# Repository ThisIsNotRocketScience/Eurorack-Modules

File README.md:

View this project on [CADLAB.io](https://cadlab.io/node/837). 

# Eurorack-Modules

This is the central repo for all the "This is not Rocket Science" eurorack modular synth modules.

Please refer to the "Production" folder if you are looking for boards to build. You will find all the design & firmware files for our latest production versions. Artwork is NOT included. Be creative. 

All our current development & experiments can be found in the "Development" folder

Sourcecode to the firmware can be found in the Eurorack-KDS repository

Tools needed:

- Eagle 7+
- Kinetis Development Studio (or whatever the latest NXP/freescale IDE is)
- A JTAG probe to flash the initial firmware

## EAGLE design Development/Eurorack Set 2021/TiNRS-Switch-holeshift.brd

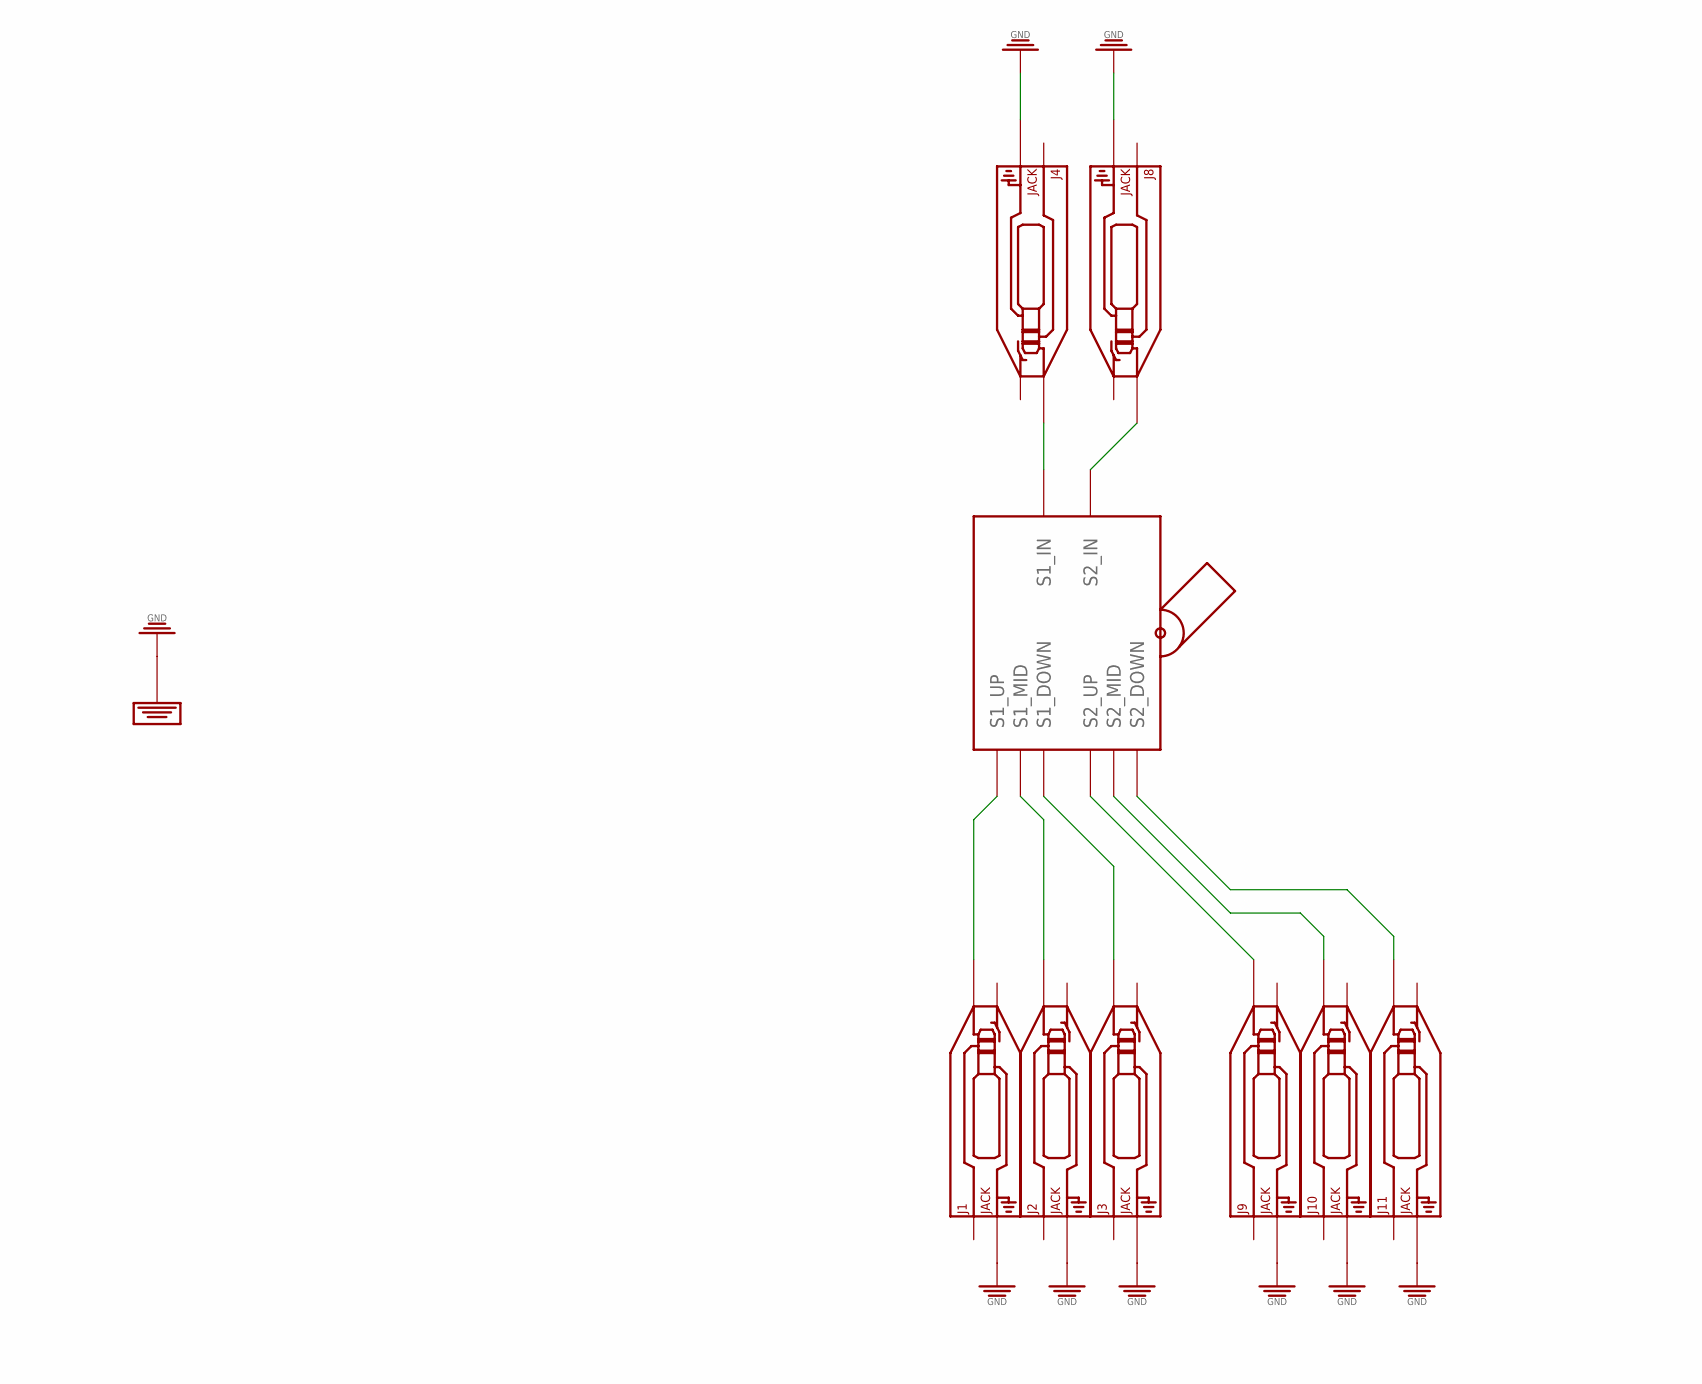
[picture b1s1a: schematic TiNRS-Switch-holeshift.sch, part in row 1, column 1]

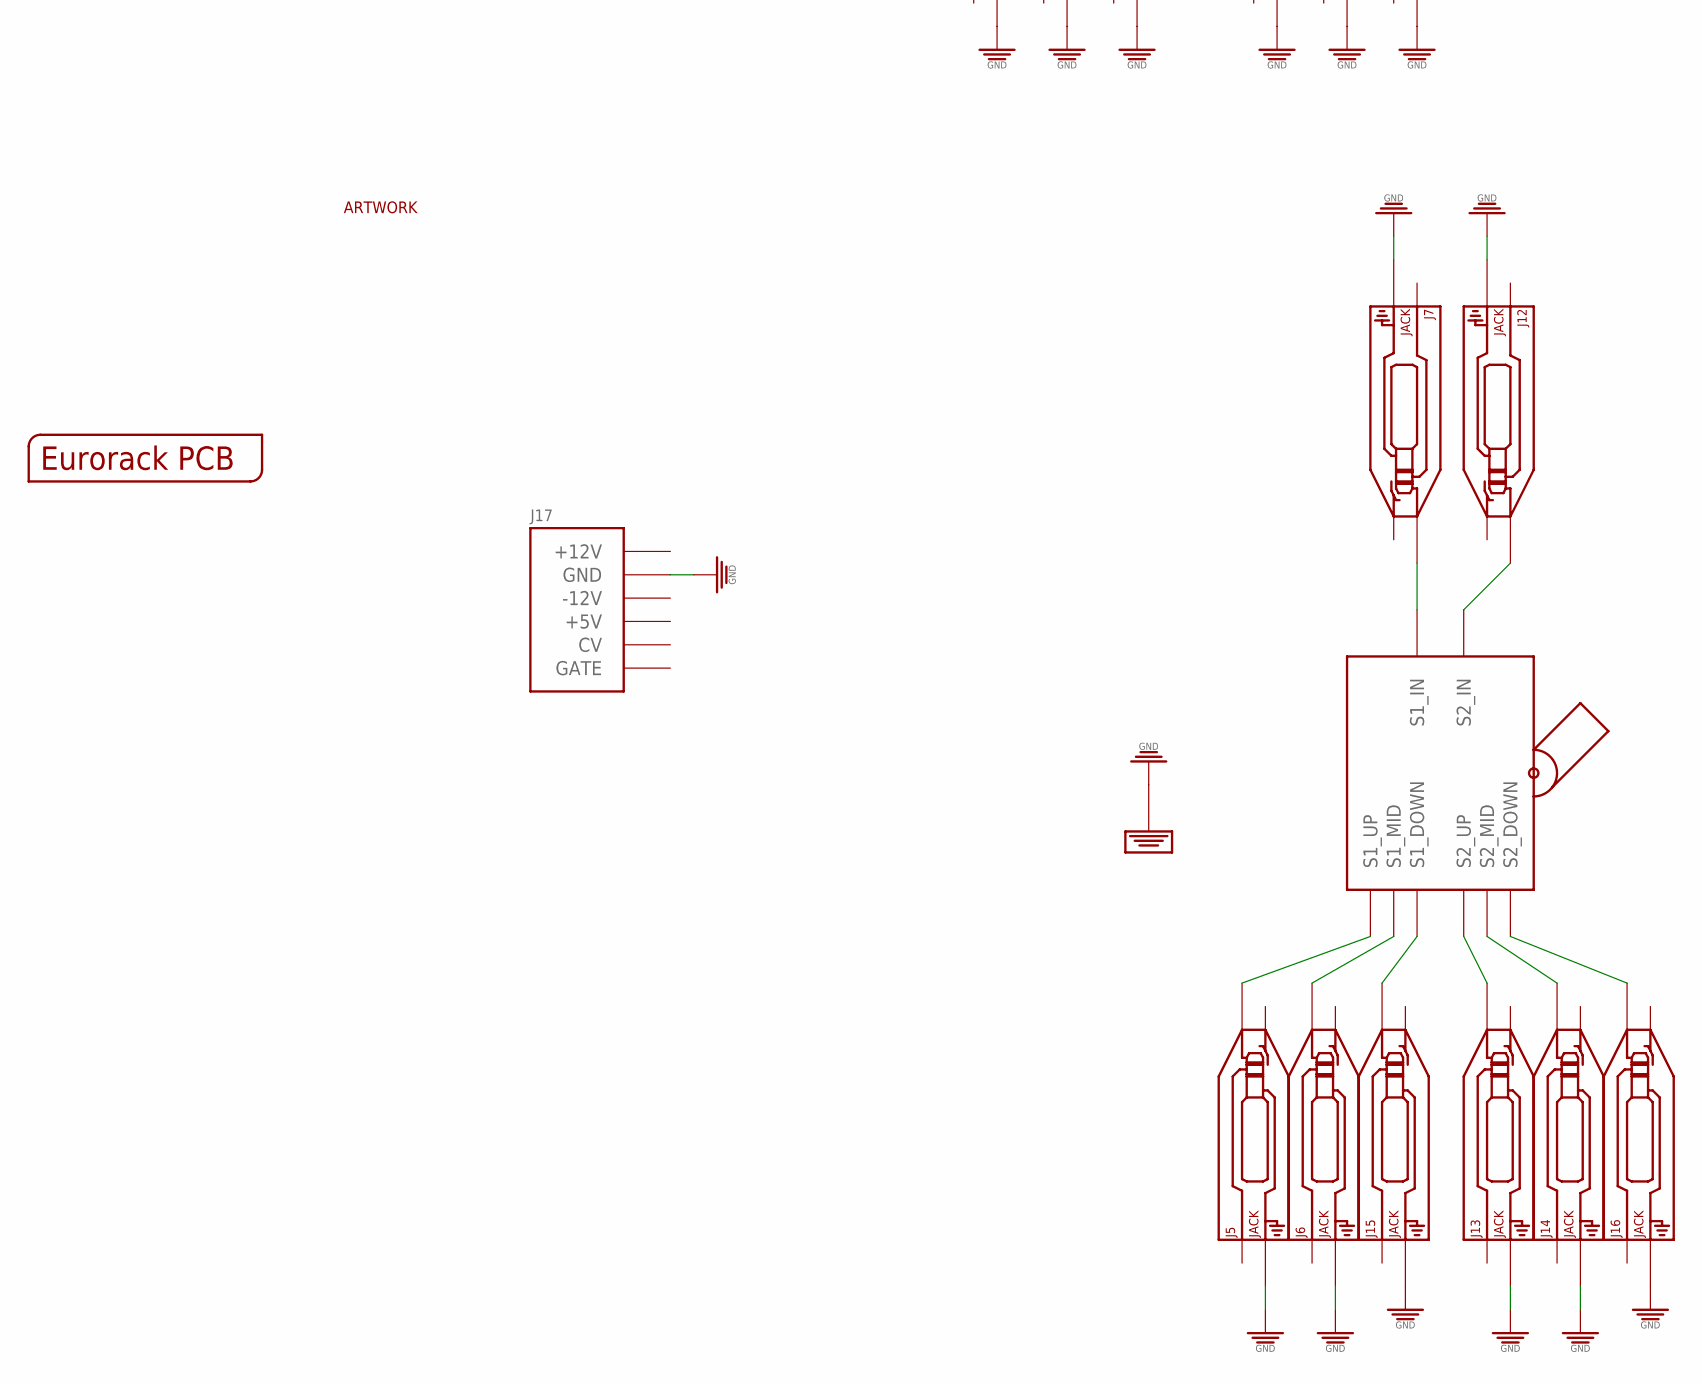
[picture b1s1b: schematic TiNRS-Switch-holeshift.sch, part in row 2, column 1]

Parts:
J1, J2, J3, J4, J5, J6, J7, J8, J9, J10, J11, J12, J13, J14, J15, J16: JACK; 3.5MM-JACK-SWITCH-13MM-NOHOLES
J17: POWER_SHROUDED_NOTEXT; POWER_16_SHROUDED_NOTEXT
PCB1: EURORACK_PCB6HP; EURORACK6HPPCB
U$2, U$5: TS-23E01
U$4: TINRS_ARTWORKTINYDATE; JUSTATINYROCKET_DATECODE

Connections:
GND: J1.RING_B@1 (RING), J1.RING_T@3 (RING), J2.RING_B@1 (RING), J2.RING_T@3 (RING), J3.RING_B@1 (RING), J3.RING_T@3 (RING), J4.RING_B@1 (RING), J4.RING_T@3 (RING), J5.RING_B@1 (RING), J5.RING_T@3 (RING), J6.RING_B@1 (RING), J6.RING_T@3 (RING), J7.RING_B@1 (RING), J7.RING_T@3 (RING), J8.RING_B@1 (RING), J8.RING_T@3 (RING), J9.RING_B@1 (RING), J9.RING_T@3 (RING), J10.RING_B@1 (RING), J10.RING_T@3 (RING), J11.RING_B@1 (RING), J11.RING_T@3 (RING), J12.RING_B@1 (RING), J12.RING_T@3 (RING), J13.RING_B@1 (RING), J13.RING_T@3 (RING), J14.RING_B@1 (RING), J14.RING_T@3 (RING), J15.RING_B@1 (RING), J15.RING_T@3 (RING), J16.RING_B@1 (RING), J16.RING_T@3 (RING), J17.3 (GND), J17.4 (GND), J17.5 (GND), J17.6 (GND), J17.7 (GND), J17.8 (GND), U$2.P$9 (GND), U$2.P$10 (GND), U$2.P$11 (GND), U$2.P$12 (GND), U$5.P$9 (GND), U$5.P$10 (GND), U$5.P$11 (GND), U$5.P$12 (GND)
unnamed: J4.TIP_B@1 (TIP), J4.TIP_T@3 (TIP), U$2.S1_SRC (S1_IN)
unnamed: J8.TIP_B@1 (TIP), J8.TIP_T@3 (TIP), U$2.S2_SRC (S2_IN)
unnamed: J1.TIP_B@1 (TIP), J1.TIP_T@3 (TIP), U$2.S1_UP
unnamed: J2.TIP_B@1 (TIP), J2.TIP_T@3 (TIP), U$2.S1_MID
unnamed: J3.TIP_B@1 (TIP), J3.TIP_T@3 (TIP), U$2.S1_DOWN
unnamed: J9.TIP_B@1 (TIP), J9.TIP_T@3 (TIP), U$2.S2_UP
unnamed: J10.TIP_B@1 (TIP), J10.TIP_T@3 (TIP), U$2.S2_MID
unnamed: J11.TIP_B@1 (TIP), J11.TIP_T@3 (TIP), U$2.S2_DOWN
unnamed: J6.TIP_B@1 (TIP), J6.TIP_T@3 (TIP), U$5.S1_MID
unnamed: J5.TIP_B@1 (TIP), J5.TIP_T@3 (TIP), U$5.S1_UP
unnamed: J7.TIP_B@1 (TIP), J7.TIP_T@3 (TIP), U$5.S1_SRC (S1_IN)
unnamed: J12.TIP_B@1 (TIP), J12.TIP_T@3 (TIP), U$5.S2_SRC (S2_IN)
unnamed: J13.TIP_B@1 (TIP), J13.TIP_T@3 (TIP), U$5.S2_UP
unnamed: J15.TIP_B@1 (TIP), J15.TIP_T@3 (TIP), U$5.S1_DOWN
unnamed: J14.TIP_B@1 (TIP), J14.TIP_T@3 (TIP), U$5.S2_MID
unnamed: J16.TIP_B@1 (TIP), J16.TIP_T@3 (TIP), U$5.S2_DOWN

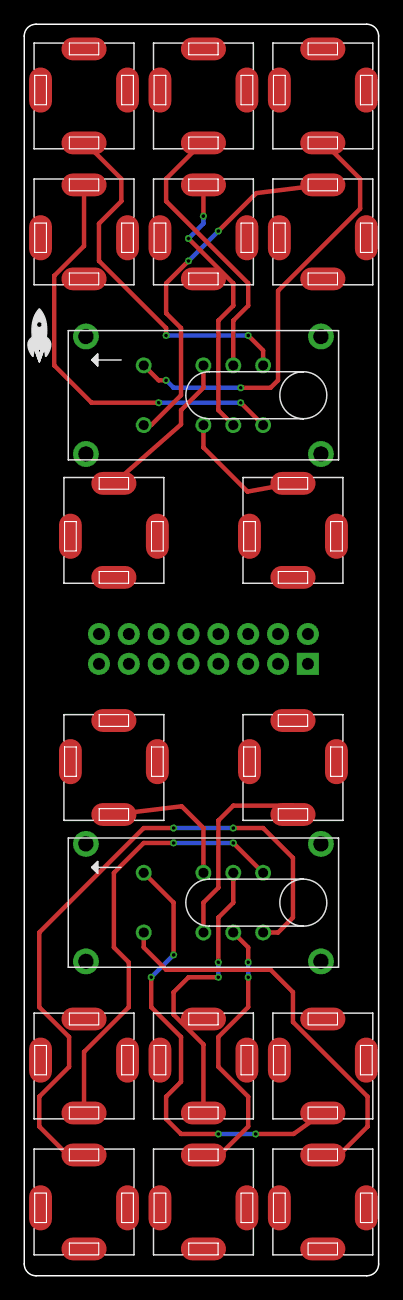
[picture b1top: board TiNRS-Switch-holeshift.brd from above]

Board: 2 copper layers, 30.2 x 106.5 mm, 21 parts (1 on the bottom side), 17 nets.

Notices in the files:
parts and their libraries:
SparkFun-Aesthetics: Licensing: CC v3.0 Share-Alike You are welcome to use this library for commercial purposes.
